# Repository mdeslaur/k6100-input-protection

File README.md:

# k6100 Input Protection Board

This is a reproduction of the Wells-Gardner k6100 Input Protection board
added to later date P314 boards.

It may not be worth adding these anymore as they can also cause problems,
but YMMV.

Gerbers for JLCPCB are located in the gerbers directory.
A PDF of the schematic and a 3d render are located in the Docs directory.

Change history:  
2025-02-28 - 1.0 - Initial version  

To Do:  

Marc Deslauriers

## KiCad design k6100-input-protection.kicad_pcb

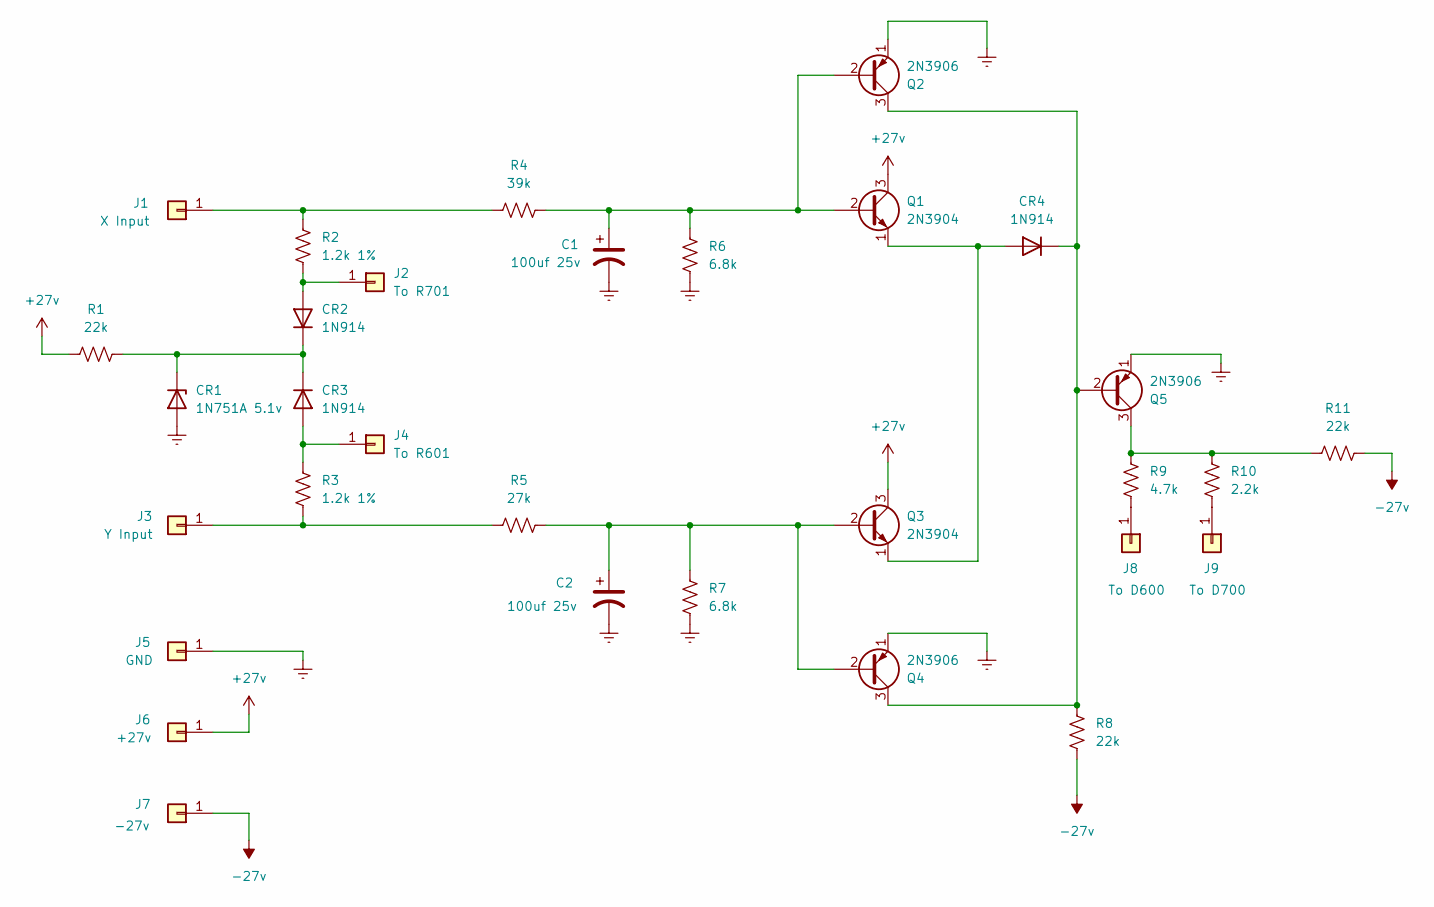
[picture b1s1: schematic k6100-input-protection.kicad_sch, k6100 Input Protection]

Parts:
C1, C2: 100uf 25v; CP_Axial_L18.0mm_D6.5mm_P25.00mm_Horizontal
CR1: 1N751A 5.1v; D_DO-35_SOD27_P12.70mm_Horizontal
CR2, CR3, CR4: 1N914; D_DO-35_SOD27_P12.70mm_Horizontal
J1: X Input; TestPoint_Bridge_Pitch2.54mm_Drill1.3mm
J2: To R701; TestPoint_Bridge_Pitch2.54mm_Drill1.3mm
J3: Y Input; TestPoint_Bridge_Pitch2.54mm_Drill1.3mm
J4: To R601; TestPoint_Bridge_Pitch2.54mm_Drill1.3mm
J5: GND; TestPoint_Bridge_Pitch2.54mm_Drill1.3mm
J6: +27v; TestPoint_Bridge_Pitch2.54mm_Drill1.3mm
J7: -27v; TestPoint_Bridge_Pitch2.54mm_Drill1.3mm
J8: To D600; TestPoint_Bridge_Pitch2.54mm_Drill1.3mm
J9: To D700; TestPoint_Bridge_Pitch2.54mm_Drill1.3mm
Q1, Q3: 2N3904; TO-92_Wide_inv
Q2, Q4, Q5: 2N3906; TO-92_Wide_inv
R1, R8, R11: 22k; R_Axial_DIN0309_L9.0mm_D3.2mm_P12.70mm_Horizontal
R2, R3: 1.2k 1%; R_Axial_DIN0309_L9.0mm_D3.2mm_P12.70mm_Horizontal
R4: 39k; R_Axial_DIN0309_L9.0mm_D3.2mm_P12.70mm_Horizontal
R5: 27k; R_Axial_DIN0309_L9.0mm_D3.2mm_P12.70mm_Horizontal
R6, R7: 6.8k; R_Axial_DIN0309_L9.0mm_D3.2mm_P12.70mm_Horizontal
R9: 4.7k; R_Axial_DIN0207_L6.3mm_D2.5mm_P15.24mm_Horizontal
R10: 2.2k; R_Axial_DIN0207_L6.3mm_D2.5mm_P15.24mm_Horizontal

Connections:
+27v: J6.1, Q1.3 (C), Q3.3 (C), R1.1
-27v: J7.1, R8.2, R11.2
Earth: C1.2, C2.2, CR1.2 (A), J5.1, Q2.1 (E), Q4.1 (E), Q5.1 (E), R6.2, R7.2
unnamed: CR1.1 (K), CR2.1 (K), CR3.1 (K), R1.2
unnamed: CR2.2 (A), J2.1, R2.2
unnamed: CR3.2 (A), J4.1, R3.1
unnamed: CR4.2 (A), Q1.1 (E), Q3.1 (E)
unnamed: CR4.1 (K), Q2.3 (C), Q4.3 (C), Q5.2 (B), R8.1
unnamed: J1.1, R2.1, R4.1
unnamed: J3.1, R3.2, R5.1
unnamed: J8.1, R9.2
unnamed: J9.1, R10.2
unnamed: C1.1, Q1.2 (B), Q2.2 (B), R4.2, R6.1
unnamed: C2.1, Q3.2 (B), Q4.2 (B), R5.2, R7.1
unnamed: Q5.3 (C), R9.1, R10.1, R11.1

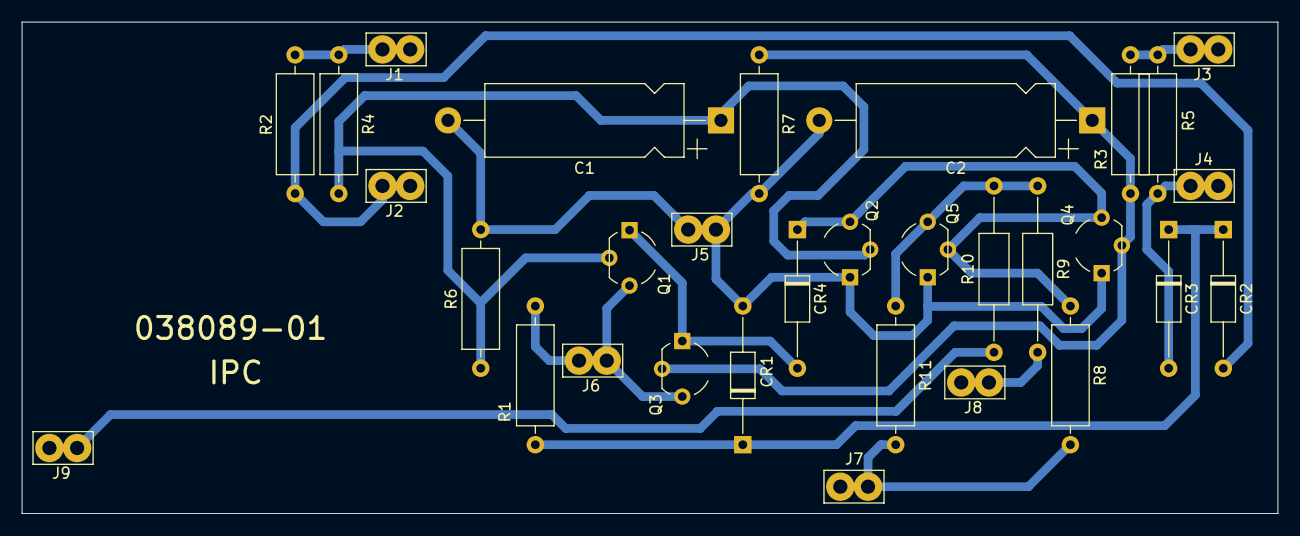
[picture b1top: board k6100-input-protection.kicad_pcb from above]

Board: 2 copper layers, 115.0 x 45.0 mm, 31 parts (0 on the bottom side), 15 nets.

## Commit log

2025-03-01 added schematic
